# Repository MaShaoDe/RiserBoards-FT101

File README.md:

# RB Riser Boards for Yaesu FT-101 and Sommerkamp FT-277 Transceivers

*Because aligning a plug-in card with your nose inside the chassis is a tradition no OM or YL needs to keep.*

**No CAD skills needed, no special tools, no excuses.** Grab the Gerber ZIP, upload it to JLCPCB, order a card edge connector, and a week later the postman brings you a pack of shiny gold fingered boards. Heat up the iron, solder 36 joints, beep them through, and your FT-101 opens up like it never did before. That is the DIY spirit that built ham radio: you build it, you understand it, you fix it. Let's go!

The Yaesu FT-101 family, sold in Europe as the Sommerkamp FT-277, earned the nickname "the workhorse" for good reason: almost every circuit sits on a plug-in card that drops into an edge connector in the chassis. Great for service. Less great when you want to measure a card while it is running, because then it is buried between its neighbours.

A riser board solves that, QSL? It plugs into the socket in the radio, and the card plugs into the riser. The card now stands about 10 cm higher, in line with its original position, and every trimmer, test point and component is within reach of your probe. Each contact also gets its own test pad on the riser, top and bottom.

## Which radios?

Every model of the original series with plug-in cards:

| Brand | Models |
|---|---|
| Yaesu | FT-101 (Mk I, Mk II), FT-101B, FT-101E, FT-101EE, FT-101EX, FT-101F, FT-101FE, FT-101FX (plus the Japanese BS and ES versions) |
| Sommerkamp | FT-277, FT-277B, FT-277E, FT-277EE |

Not for the FT-101Z and FT-101ZD. Despite the name they are a different design without plug-in cards. Sorry, Z owners, negative copy on this one.

## Which riser for which card?

The number in the name is the count of contacts per side. That is also how to pick one: count the fingers on one side of your card, or measure the width of the finger zone.

| Riser | Contacts | Finger zone | Cards | Status |
|---|---|---|---|---|
| [RB10](hardware/riser-2x10) | 2x10 | 42 mm | PB-1292 noise blanker | V0.1 Gerber ready, untested |
| [RB14](hardware/riser-2x14) | 2x14 | 57 mm | PB-1184A modulator and oscillator | V0.1 Gerber ready, untested |
| [RB18](hardware/riser-2x18) | 2x18 | 73 mm | PB-1180B HF IF, PB-1181B RF, PB-1314 regulator | **V0.1 prototype ordered** |
| [RB22](hardware/riser-2x22) | 2x22 | 89 mm | PB-1183B IF, PB-1315A AF | V0.1 Gerber ready, untested |

Card names vary between production runs. If your card has the right width, it fits.

## Build one in four steps

1. **Download** the Gerber ZIP of your riser: [RB10](hardware/riser-2x10/RB10_V0.1_gerber.zip), [RB14](hardware/riser-2x14/RB14_V0.1_gerber.zip), [RB18](hardware/riser-2x18/RB18_V0.1_gerber.zip) or [RB22](hardware/riser-2x22/RB22_V0.1_gerber.zip).
2. **Order** bare boards at JLCPCB or a similar maker. Settings are in [docs/ordering.md](docs/ordering.md). The one thing you must not forget: **Gold Fingers: Yes**.
3. **Buy** one card edge connector per board, see [docs/bom.md](docs/bom.md).
4. **Solder** the connector and start measuring, see [docs/assembly.md](docs/assembly.md).

Total cost for five RB18 boards plus connectors: roughly the price of a nice dinner for two, and a lot less than a burnt card. Share the spare boards with the OMs in your club and the whole local net is QRV for service.

## What is on the board

- FR4, 1.6 mm, 105 mm long, in-line design: the card stands straight above the socket
- Hard gold edge fingers on both sides with a bevelled tip
- 2 mm traces, top and bottom kept separate, all covered by solder mask
- One test pad per contact on both sides, in line with the card's pins
- Clear silkscreen: riser type, compatible radios, "COMPONENT SIDE" and an arrow towards the radio, so the card goes in the right way round
- No pin numbers printed. The cards in this family number their pins in different directions, so the riser would be wrong on half of them. Read the number on the card itself.

## A word about RF and IF cards

The riser makes the signal path about 10 cm longer. Supply voltages, bias and audio do not care. Tuned RF and IF circuits (PB-1180B, PB-1181B, PB-1183B) may, and you would rather not hunt self-made QRM. Use the riser there to measure voltages and levels, and do the fine alignment with the card back in its own socket.

## Contents

- [docs/specification.md](docs/specification.md): measurements, design decisions, open questions
- [docs/ordering.md](docs/ordering.md): Gerber export and order settings
- [docs/bom.md](docs/bom.md): parts to buy
- [docs/assembly.md](docs/assembly.md): soldering, checking and using the riser
- `hardware/`: one folder per riser with KiCad board, Gerber files and pictures
- `hardware/tools/gen_riser.py`: generator for all variants (`python3 gen_riser.py 10|14|18|22`)

## Licenses

- Hardware (KiCad files, Gerber files, generator): CERN-OHL-P-2.0
- Documentation and pictures: CC-BY-4.0

See [LICENSE.md](LICENSE.md). You may build, sell and modify the boards. If you change the design, please give it a name of your own and do not call it RB10, RB14, RB18 or RB22, so that the tested original stays recognisable.

## Disclaimer

Use at your own risk. The FT-101 carries high voltages in the PA section, and the riser does not change that. This project has no connection to Yaesu or Sommerkamp. The names are used only to state compatibility.

## Contributing

Measurements of other cards, corrections, photos and stories of successful repairs are welcome. Open an issue or a pull request, we copy you 5 and 9.

Questions, ideas or wishes for changes? Just call in by opening an issue on GitHub. No promises on what gets built or when, this is a hobby project run in spare time between QSOs, but every message is read and the band is always open.

## Thank you

To Yaesu for building a radio that people still repair with love fifty years later, to Sommerkamp for bringing it to Europe, to everyone who keeps the service manuals and board lists online, and to every OM and YL who keeps an old workhorse on the air.

May your filaments glow and your SWR stay flat.

73 de Marcel (MaShaoDe)

Copyright 2026 FerienBSD aka Marcel Sauder (MaShaoDe)

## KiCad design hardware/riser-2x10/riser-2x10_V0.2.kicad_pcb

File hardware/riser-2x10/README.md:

# RB10: Riser 2x10 (20 contacts)

Status: V0.1, Gerber files exported from KiCad 9. Same design rules as the RB18. Will be ordered after the RB18 prototype has passed its test.

For cards: PB-1292 (noise blanker)

| Component side | Rear side |
|---|---|
|  |  |

## Files

| File | Content |
|---|---|
| `riser-2x10.kicad_pcb` | KiCad board (KiCad 8 format, opens in KiCad 9) |
| `RB10_V0.1_gerber.zip` | Gerber and drill files, ready to upload to the PCB maker |
| `gerber/` | The same Gerber files, unpacked |
| `gerber-front.png`, `gerber-back.png` | Rendered from the Gerber files |
| `preview.png` | Quick preview from the generator |
| `riser-2x10_V0.2.kicad_pcb`, `preview_V0.2.png` | V0.2 (new silkscreen, see CHANGELOG), Gerber files pending |
| `../tools/gen_riser.py` | Generator. `python3 gen_riser.py 10` rebuilds both files. |

## Board

| Item | Value |
|---|---|
| Material | FR4, 1.6 mm, 2 layers, 1 oz |
| Length | 105 mm (finger tip to connector edge) |
| Finger zone | 11 mm long, 42 mm wide |
| Upper part | 47 mm wide, 45 degree step, rounded corners (R 1.5 mm) |
| Contact pitch | 3.96 mm, contact field 35.64 mm |
| Edge fingers | 2.0 x 9.0 mm, 0.6 mm back from the tip, both sides, hard gold |
| Traces | 2.0 mm, straight, top and bottom separate |
| Test pads | round 2.6 mm, 12 mm from the connector edge, both sides |
| Connector pads | 2.0 x 5.0 mm, 0.5 mm from the connector edge, both sides |
| Silkscreen | centre texts scaled to the board width |

## Ordering and assembly

- Order settings: [../../docs/ordering.md](../../docs/ordering.md)
- Connector (20 contacts, 3.96 mm): [../../docs/bom.md](../../docs/bom.md)
- Soldering and use: [../../docs/assembly.md](../../docs/assembly.md)

## Revision history

| Version | Date | Change |
|---|---|---|
| V0.1 | 2026-11-11 | First layout, generated with the RB18 rules, Gerber exported |

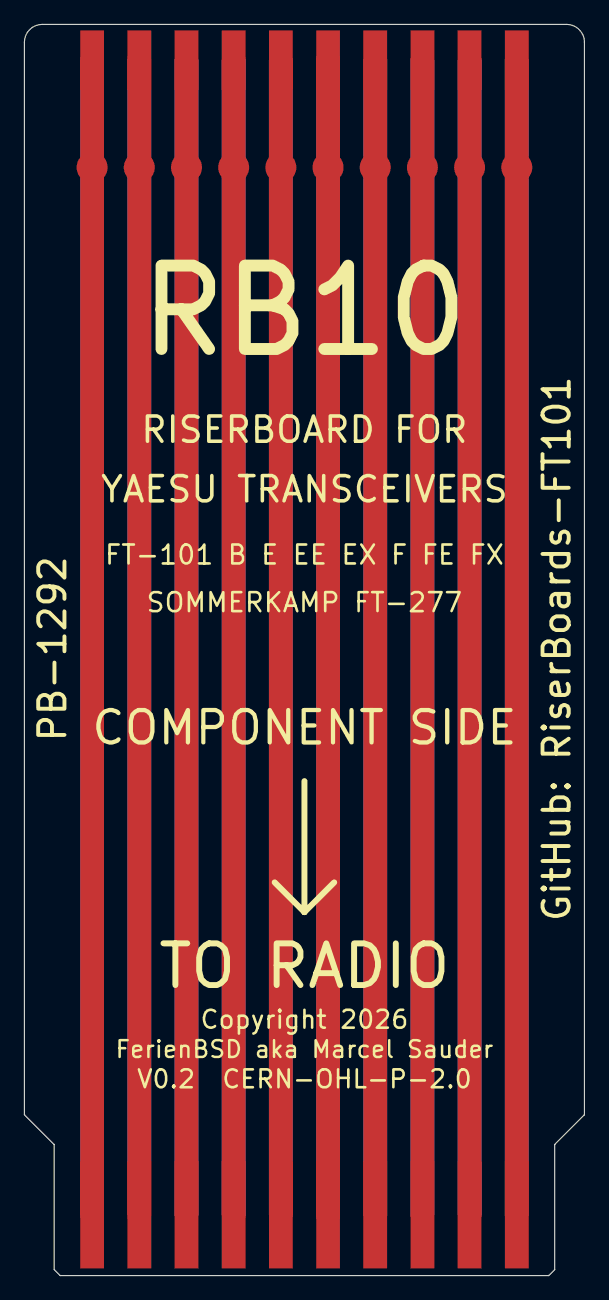
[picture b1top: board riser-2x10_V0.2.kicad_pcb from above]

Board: 2 copper layers, 47.0 x 105.0 mm, 3 parts (0 on the bottom side), 20 nets.

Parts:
J1: EdgeFingers_2x10
J2: ConnectorPads_2x10
TP1: TestPads_2x10

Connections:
POS01B: J1.1B, J2.1B, TP1.1B
POS01F: J1.1, J2.1, TP1.1
POS02B: J1.2B, J2.2B, TP1.2B
POS02F: J1.2, J2.2, TP1.2
POS03B: J1.3B, J2.3B, TP1.3B
POS03F: J1.3, J2.3, TP1.3
POS04B: J1.4B, J2.4B, TP1.4B
POS04F: J1.4, J2.4, TP1.4
POS05B: J1.5B, J2.5B, TP1.5B
POS05F: J1.5, J2.5, TP1.5
POS06B: J1.6B, J2.6B, TP1.6B
POS06F: J1.6, J2.6, TP1.6
POS07B: J1.7B, J2.7B, TP1.7B
POS07F: J1.7, J2.7, TP1.7
POS08B: J1.8B, J2.8B, TP1.8B
POS08F: J1.8, J2.8, TP1.8
POS09B: J1.9B, J2.9B, TP1.9B
POS09F: J1.9, J2.9, TP1.9
POS10B: J1.10B, J2.10B, TP1.10B
POS10F: J1.10, J2.10, TP1.10

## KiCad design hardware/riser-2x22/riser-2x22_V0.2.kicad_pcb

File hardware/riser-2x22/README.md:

# RB22: Riser 2x22 (44 contacts)

Status: V0.1, Gerber files exported from KiCad 9. Same design rules as the RB18. Will be ordered after the RB18 prototype has passed its test.

For cards: PB-1183B (IF), PB-1315A (AF)

| Component side | Rear side |
|---|---|
|  |  |

## Files

| File | Content |
|---|---|
| `riser-2x22.kicad_pcb` | KiCad board (KiCad 8 format, opens in KiCad 9) |
| `RB22_V0.1_gerber.zip` | Gerber and drill files, ready to upload to the PCB maker |
| `gerber/` | The same Gerber files, unpacked |
| `gerber-front.png`, `gerber-back.png` | Rendered from the Gerber files |
| `preview.png` | Quick preview from the generator |
| `riser-2x22_V0.2.kicad_pcb`, `preview_V0.2.png` | V0.2 (new silkscreen, see CHANGELOG), Gerber files pending |
| `../tools/gen_riser.py` | Generator. `python3 gen_riser.py 22` rebuilds both files. |

## Board

| Item | Value |
|---|---|
| Material | FR4, 1.6 mm, 2 layers, 1 oz |
| Length | 105 mm (finger tip to connector edge) |
| Finger zone | 11 mm long, 89 mm wide |
| Upper part | 94 mm wide, 45 degree step, rounded corners (R 1.5 mm) |
| Contact pitch | 3.96 mm, contact field 83.16 mm |
| Edge fingers | 2.0 x 9.0 mm, 0.6 mm back from the tip, both sides, hard gold |
| Traces | 2.0 mm, straight, top and bottom separate |
| Test pads | round 2.6 mm, 12 mm from the connector edge, both sides |
| Connector pads | 2.0 x 5.0 mm, 0.5 mm from the connector edge, both sides |
| Silkscreen | centre texts scaled to the board width |

## Ordering and assembly

- Order settings: [../../docs/ordering.md](../../docs/ordering.md)
- Connector (44 contacts, 3.96 mm): [../../docs/bom.md](../../docs/bom.md)
- Soldering and use: [../../docs/assembly.md](../../docs/assembly.md)

## Revision history

| Version | Date | Change |
|---|---|---|
| V0.1 | 2026-11-11 | First layout, generated with the RB18 rules, Gerber exported |

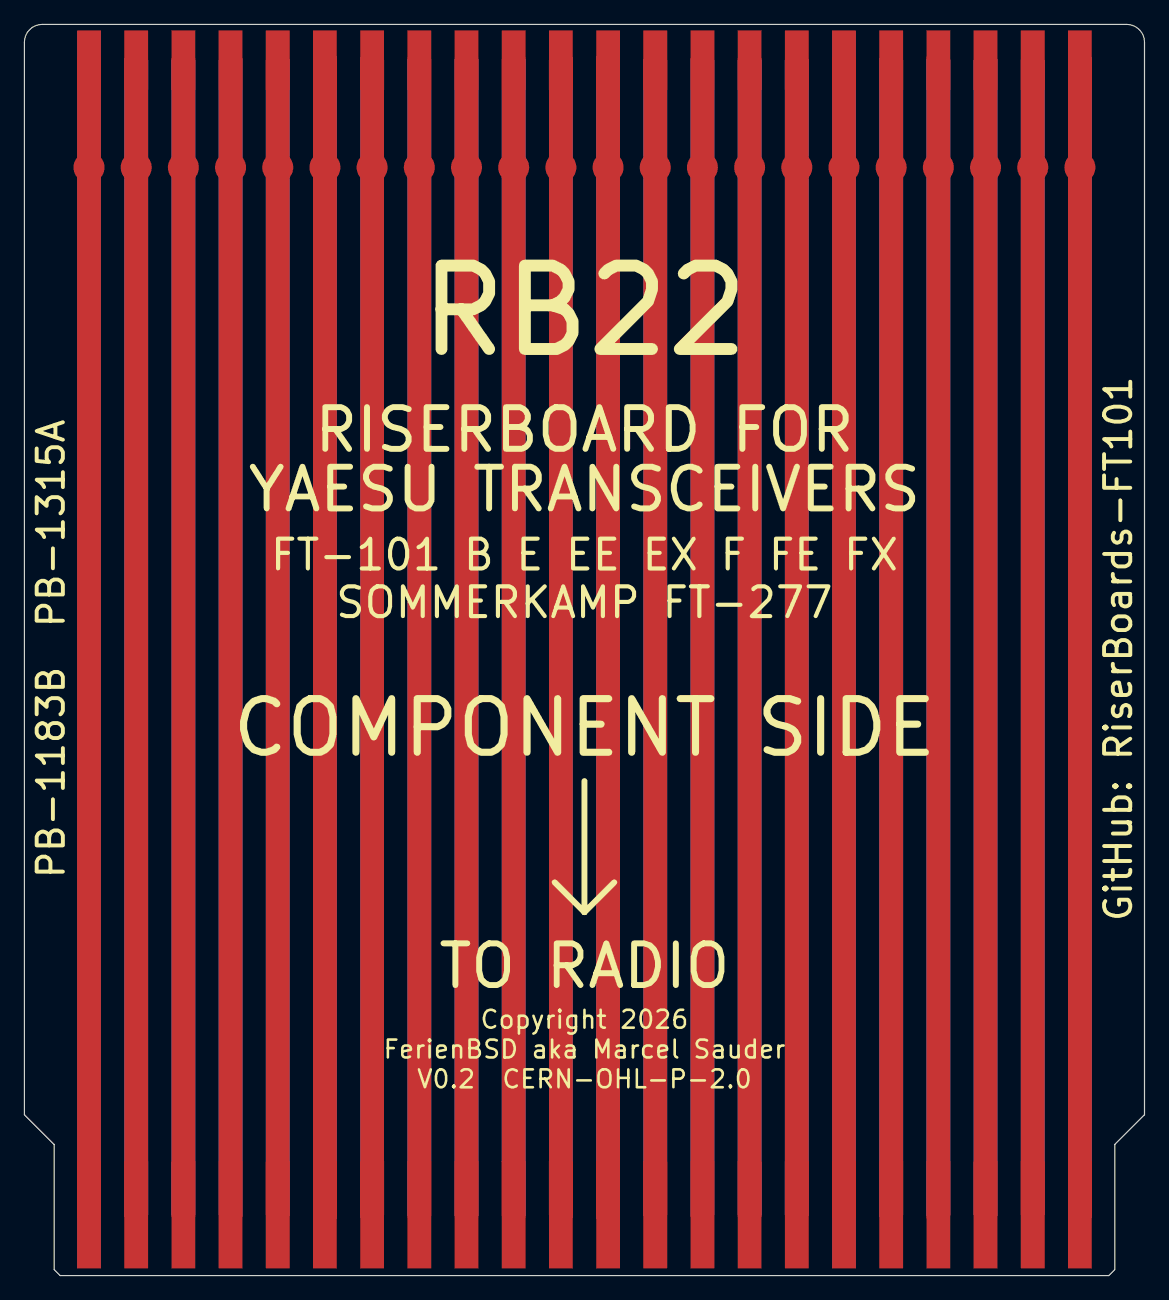
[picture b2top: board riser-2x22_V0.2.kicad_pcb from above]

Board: 2 copper layers, 94.0 x 105.0 mm, 3 parts (0 on the bottom side), 44 nets.

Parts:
J1: EdgeFingers_2x22
J2: ConnectorPads_2x22
TP1: TestPads_2x22

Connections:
POS01B: J1.1B, J2.1B, TP1.1B
POS01F: J1.1, J2.1, TP1.1
POS02B: J1.2B, J2.2B, TP1.2B
POS02F: J1.2, J2.2, TP1.2
POS03B: J1.3B, J2.3B, TP1.3B
POS03F: J1.3, J2.3, TP1.3
POS04B: J1.4B, J2.4B, TP1.4B
POS04F: J1.4, J2.4, TP1.4
POS05B: J1.5B, J2.5B, TP1.5B
POS05F: J1.5, J2.5, TP1.5
POS06B: J1.6B, J2.6B, TP1.6B
POS06F: J1.6, J2.6, TP1.6
POS07B: J1.7B, J2.7B, TP1.7B
POS07F: J1.7, J2.7, TP1.7
POS08B: J1.8B, J2.8B, TP1.8B
POS08F: J1.8, J2.8, TP1.8
POS09B: J1.9B, J2.9B, TP1.9B
POS09F: J1.9, J2.9, TP1.9
POS10B: J1.10B, J2.10B, TP1.10B
POS10F: J1.10, J2.10, TP1.10
POS11B: J1.11B, J2.11B, TP1.11B
POS11F: J1.11, J2.11, TP1.11
POS12B: J1.12B, J2.12B, TP1.12B
POS12F: J1.12, J2.12, TP1.12
POS13B: J1.13B, J2.13B, TP1.13B
POS13F: J1.13, J2.13, TP1.13
POS14B: J1.14B, J2.14B, TP1.14B
POS14F: J1.14, J2.14, TP1.14
POS15B: J1.15B, J2.15B, TP1.15B
POS15F: J1.15, J2.15, TP1.15
POS16B: J1.16B, J2.16B, TP1.16B
POS16F: J1.16, J2.16, TP1.16
POS17B: J1.17B, J2.17B, TP1.17B
POS17F: J1.17, J2.17, TP1.17
POS18B: J1.18B, J2.18B, TP1.18B
POS18F: J1.18, J2.18, TP1.18
POS19B: J1.19B, J2.19B, TP1.19B
POS19F: J1.19, J2.19, TP1.19
POS20B: J1.20B, J2.20B, TP1.20B
POS20F: J1.20, J2.20, TP1.20
POS21B: J1.21B, J2.21B, TP1.21B
POS21F: J1.21, J2.21, TP1.21
POS22B: J1.22B, J2.22B, TP1.22B
POS22F: J1.22, J2.22, TP1.22

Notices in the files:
hardware/riser-2x10/riser-2x10_V0.2.kicad_pcb:
V0.2  CERN-OHL-P-2.0
